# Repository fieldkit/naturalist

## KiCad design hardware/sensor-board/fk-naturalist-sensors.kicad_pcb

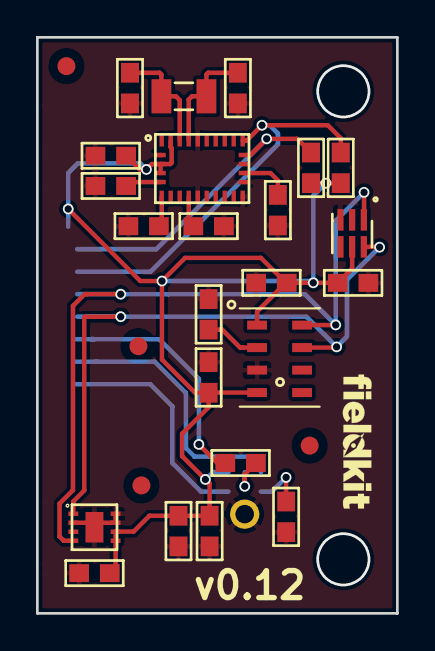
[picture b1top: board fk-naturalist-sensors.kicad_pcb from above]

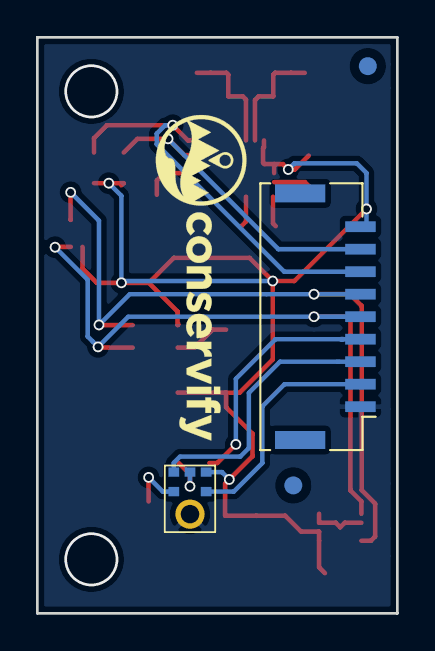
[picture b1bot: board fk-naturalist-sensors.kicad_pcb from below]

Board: 2 copper layers, 20.0 x 32.0 mm, 31 parts (4 on the bottom side), 18 nets.

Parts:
C1, C2, C3, C9, C10: 100nF; CAP-0603
C4, C6: 1uF; CAP-0603
C5: 10uF; CAP-0603
C7: 220pF; CAP-0603
C8, C11: 22pF; CAP-0603
J1: CONN_01x09; Molex_CLIK-Mate_502382-0970_1x09_P1.25mm_Vertical
M1, M2, M5, M6, M9, M10: FIDUCIAL; FIDUCIAL-1MM
R1, R3, R4, R5: 10K; RES-0603
R2: 68R; RES-0603
R6, R7: 4.7K; RES-0603
U1: MPL3115A2; DFN-8-1EP_5x2.55mm_Pitch1.25mm_98ASA002260D
U2: SHT31; SHT3x
U3: SPH0645; SPH0645LM4H-B
U4: TSL2591
U5: BNO055
Y1: FC-135; ABS07

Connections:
3V3: C2.1, C3.1, C4.1, C5.1, C6.1, C7.1, C9.2, J1.9, R6.2, R7.2, U1.1, U1.4, U2.5, U2.6, U3.5, U4.5, U5.3, U5.4, U5.28
/I2S_BCLK: J1.2, U3.4
/I2S_DATA: J1.4, R2.2
/I2S_WS: J1.3, U3.1
/SCL: J1.6, U1.8, U2.4, U4.1
/SCL2: J1.8, R7.1, U5.19
/SDA: J1.5, U1.7, U2.1, U4.6
/SDA2: J1.7, R6.1, U5.20
GND: C1.2, C2.2, C3.2, C4.2, C5.2, C6.2, C7.2, C8.2, C9.1, C10.1, C11.2, J1.1, R1.1, R3.2, R4.2, R5.2, U1.3, U2.2, U2.7, U2.8, U2.PAD, U3.3, U4.3, U5.2, U5.10, U5.15, U5.16, U5.18, U5.25
unnamed: C1.1, U1.2
unnamed: C8.1, U5.27, Y1.1
unnamed: C10.2, U5.9
unnamed: C11.1, U5.26, Y1.2
unnamed: R1.2, U3.2
unnamed: R2.1, U3.6
unnamed: R3.1, U5.17
unnamed: R4.1, U5.6
unnamed: R5.1, U5.5

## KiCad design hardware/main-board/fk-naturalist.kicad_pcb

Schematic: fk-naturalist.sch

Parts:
BT1: BATTERY_CELL; BAT_CR1210
C1, C6, C12, C21, C26, C27: 1uF; CAP-0603
C2, C32: 47uF; CAP-0603
C3, C4: 18pF; CAP-0603
C5, C7, C8, C9, C11, C13, C15, C16, C18, C33, C35: 100nF; CAP-0603
C10, C19, C20: 4.7uF; CAP-0603
C14: 4.7nF; CAP-0603
C17, C22, C24, C31, C34: 10uF; CAP-0603
C23, C29: 470pF; CAP-0603
C25, C30: 2.2uF; CAP-0603
C28: 10nF; CAP-0603
D1: Orange; LED-0603
D2, D9: Green; LED-0603
D3: Yellow; LED-0603
D7: PMEG3020CPA; SOT-1016
D8: PRTR5V0U2X; SOT-143B
D10, D11: Red; LED-0603
F1: MF-PSMF050X-2; MF-PSMF020X
J1, J11: RF-SMA-EDGE
J2, J12, J14: CONN_01x02; SJ_OPEN
J3, J10: S2B-PH-SM4-TB
J4: Conn_01x01; Socket_Strip_Straight_1x01_Pitch2.54mm
J5: CONN_01x03_SERIAL; Molex_CLIK-Mate_502382-0370_1x03_P1.25mm_Vertical
J6: CONN_01x09; Molex_CLIK-Mate_502382-0970_1x09_P1.25mm_Vertical
J7: CONN_02x05_SWD; HDR_02x05_Pitch1.27mm_SMD_SWD
J8: CONN_01x02; Molex_CLIK-Mate_502382-0270_1x02_P1.25mm_Vertical
J9: MICRO-USB
J13: CONN_01x06; JST_SH_BM06B-SRSS-TB_1x06-1MP_P1.00mm_Vertical
L1, L2, L3: BLM18KG221SN1D; IND-0603
M1, M3, M4, M6: MOUNT_HOLE; HOLE_NPTH_2.54MM
M2, M5, M8, M9, M10, M11: FIDUCIAL; FIDUCIAL-1MM
M7: MICRO-SD
Q1: 2N7002LT1G; SOT-23
R1, R2, R11, R13, R23: 100K; RES-0603
R3, R25, R33: 2K2; RES-0603
R4, R5, R37, R39, R40: 1K; RES-0603
R6, R7, R8, R17, R32, R34: 10K; RES-0603
R9, R10, R30: 330R; RES-0603
R12, R14: 165.7K; RES-0603
R21: 1K18; RES-0603
R22: 46K4; RES-0603
R24: 2K94; RES-0603
R31: 1M; RES-0603
R35, R36, R42, R43: 4.7K; RES-0603
R41: 180R; RES-0603
SW1, SW2: SPNO; SW_SPST_WURTH_1
U1: ATWINC1500-MR210PA; ATMEL_ATWINC1500-MR210PA
U2: ATSAMD21G18A-AU; TQFP-48_7x7mm_Pitch0.5mm
U3: RFM95W; RFM9xW
U4: 24AA02E64; SOT-23-5_HandSoldering
U5: S25FL116K0XMFI041; SOIC-8-N-WIDE
U6: BQ24074RGTT; QFN-16_3x3mm
U7: PCF8523; SOIC-8-N
U8, U9: TL5209; SOIC-8-N
U10: FGPMMOPA6H
U11: MAX1704XX; DFN-8-1EP_3x2mm_Pitch0.5mm
U12: TPS2052B; SOIC-8-N
U13: SK6812
U14: MCP1700T-3302E/MB; SOT-89
Y1, Y2: FC-135; ABS07

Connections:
3V3: C2.1, C5.1, C8.1, C9.1, C11.1, C13.1, C15.1, C24.1, C25.1, D1.2, J2.1, J7.1, J12.1, J14.2, L1.2, R6.2, R7.2, R8.1, R11.1, R17.1, R23.2, R35.1, R36.1, R37.1, R41.1, R42.2, U2.17, U2.36, U2.44, U3.13, U4.4 (VCC), U8.3, U12.2, U13.3, U14.3 (VOUT)
5V0: C10.1, D7.1, L2.1
/A1_WIFI_RST: R1.1, U1.4, U2.7
/A2_WIFI_IRQ: U1.13, U2.8
/A3: U2.9, U13.2
/A4_GPS_EN: U2.10, U12.3
/A5_MODULE_EN: U2.47
/BAT_BACKUP: BT1.1, J13.5, U7.3 (VBAT), U10.4 (VBACKUP)
/CHG: R33.1, U6.9 (~CHG~)
/D0_RADIO_D2: J7.4, U2.45, U3.16
/D1_RADIO_D1: J7.2, U2.46, U3.15
/D2_RADIO_D0: U2.23, U3.14
/D2_WIFI_EN: R2.1, U1.22, U2.22
/D5_RADIO_CS: U2.24, U3.5
/D6_USER_SW: R10.1, U2.29
/D7_WIFI_CS: U1.16, U2.30
/D8_WIFI_WAKE: U1.11, U2.11
/D9_MODULE_EN: U9.1
/D12_SD_CS: M7.2, U2.28
/D13: Q1.1, U2.26
/D26_FLASH_CS: U2.39, U5.1 (~CS~)
/D30: J5.3, U2.37
/D31: J5.2, U2.38
/GPS_3V3: C16.1, C17.1, J12.2, L3.1, U12.7
/GPS_FIX: D11.2, U10.5 (3D-FIX)
/GPS_RX: J13.4, U2.27, U10.10 (RX)
/GPS_TX: J13.3, U2.25, U10.9 (TX)
/I2S_BCLK: J6.2, U2.15
/I2S_DATA: J6.4, U2.12
/I2S_WS: J6.3, U2.16
/MISO: M7.7, U1.17, U2.21, U3.2, U5.2 (SO/IO1)
/MODULE_3V3: C30.1, J6.9, J14.1, R13.1, U9.3
/MOSI: M7.3, U1.15, U2.19, U3.3, U5.5 (SI/IO0)
/PERIPH_3V3: C18.1, C33.1, C34.1, D2.2, D3.2, J2.2, M7.4, U1.10, U1.20, U1.23, U5.3 (~WP~/IO2), U5.7 (~HOLD~/IO3), U5.8 (VCC), U12.6
/PERIPH_EN: U2.48, U12.4
/PG: R32.1, U6.7 (~PGOOD~)
/RESET: R9.1, U2.40
/RST: J7.10, R8.2, R9.2, SW1.2
/SCK: M7.5, U1.18, U2.20, U3.4, U5.6 (SCLK)
/SCL: J6.6, R36.2, U2.32, U4.1 (SCL), U7.6 (SCL), U11.7 (SCL)
/SCL2: J6.8, U2.14
/SDA: J6.5, R35.2, U2.31, U4.3 (SDA), U7.5 (SDA), U11.8 (SDA)
/SDA2: J6.7, U2.13
/USB+: D8.2, J9.3, U2.34
/USB-: D8.3, J9.2, U2.33
/USB_ID: R30.2, U2.41
GND: BT1.2, C1.2, C2.2, C3.1, C4.1, C5.2, C6.2, C7.2, C8.2, C9.2, C10.2, C11.2, C12.1, C13.2, C14.2, C15.2, C16.2, C17.2, C18.2, C19.2, C20.2, C21.2, C22.2, C23.2, C24.2, C25.2, C26.2, C27.2, C28.1, C29.2, C30.2, C31.1, C32.2, C33.2, C34.2, C35.2, D8.1, J1.2, J1.3, J1.4, J1.5, J3.2, J5.1, J6.1, J7.3, J7.5, J7.9, J8.1, J9.5, J10.2, J11.2, J11.3, J11.4, J11.5, J13.1, M7.6, M7.MT1, M7.MT2, Q1.2, R1.2, R2.2, R12.2, R14.2, R21.1, R22.1, R24.1, R25.1, R31.2, R34.2, R39.1, R43.2, SW1.1, SW2.1, U1.9, U1.12, U1.28, U2.5, U2.18, U2.35, U2.42, U3.1, U3.8, U3.10, U4.2 (VSS), U5.4 (VSS), U6.4 (~CE~), U6.6 (EN1), U6.8 (VSS), U6.17 (PAD), U7.4 (VSS), U8.5, U8.6, U8.7, U8.8, U9.5, U9.6, U9.7, U9.8, U10.3 (GND), U10.8 (GND), U10.12 (GND), U10.19 (GND), U11.1 (CTG), U11.4 (GND), U11.9 (GND), U12.1, U13.1, U14.1 (GND)
unnamed: C1.1, U2.4
unnamed: C3.2, U2.2, Y1.1
unnamed: C4.2, U2.1, Y1.2
unnamed: C6.1, U2.43
unnamed: C7.1, L1.1, U2.6
unnamed: C14.1, J9.7, R31.1
unnamed: C22.1, R37.2, U7.8 (VDD)
unnamed: C23.1, R11.2, R12.1, U8.4
unnamed: C27.1, R40.2, U11.2 (CELL)
unnamed: C28.2, R41.2, U11.3 (VDD)
unnamed: C29.1, R13.2, R14.1, U9.4
unnamed: C31.2, C32.1, C35.1, J13.2, L3.2, U10.1 (VCC)
unnamed: D1.1, R3.1
unnamed: D2.1, R4.2
unnamed: D3.1, R5.2
unnamed: D9.1, R32.2
unnamed: D10.1, R33.2
unnamed: D11.1, R39.2
unnamed: F1.1, L2.2
unnamed: J1.1, J4.1, U3.9
unnamed: J8.2, R10.2, R17.2, SW2.2
unnamed: J9.4, R23.1, R30.1
unnamed: J11.1, U10.11 (EX_ANT)
unnamed: Q1.3, R3.2
unnamed: R4.1, U1.26
unnamed: R5.1, U1.27
unnamed: R6.1, U12.8
unnamed: R7.1, U12.5
unnamed: R21.2, U6.12 (ILIM)
unnamed: R22.2, U6.14 (TMR)
unnamed: R24.2, U6.15 (ITERM)
unnamed: R25.2, U6.16 (ISET)
unnamed: R34.1, U6.1 (TS)
unnamed: R42.1, U11.5 (ALT)
unnamed: R43.1, U11.6 (QST)
unnamed: U7.1 (XI), Y2.2
unnamed: U7.2 (XO), Y2.1
VBAT: C19.1, J10.1, R40.1, U6.2 (BAT), U6.3 (BAT)
VBUS: C20.1, C21.1, C26.1, D9.2, D10.2, U6.5 (EN2), U6.10 (OUT), U6.11 (OUT), U8.1, U8.2, U9.2, U14.2 (VIN)
VEXT: C12.2, D7.3, U6.13 (IN)
VIN: D7.2, J3.1
VUSB: D8.4, F1.2, J9.1

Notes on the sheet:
MOUNTING
SWD/JTAG
BREAKOUT
LED
SERIAL FLASH
POWER MANAGEMENT
USB-DEVICE
MCU
TX0
RX0
VIN:5-10.5V (OVP up to 28V)
1. All capacitors are NP0/COG 50V unless specified. 2. All resistors are 62.5mW 1% unless specified.
16Mbit = 2Mbytes
M2.5 size
1.27 mm (0.05")
EN2 EN1
LOW LOW
LOW HI
HI LOW
HI HI
I-INPUT LIMIT
100mA
500mA
Set by R6:1.3A
Standby
32.768kHz
12.5pF
TX1
RX1
LEDS
24AA02E64 DEVICE ID
WIFI
GPS
POWER MANAGEMENT (3V3 REGULATOR)
I2C PULLUP
LIPO GAUGE
NOTES
RTC
RFM95W
FIDUCIALS

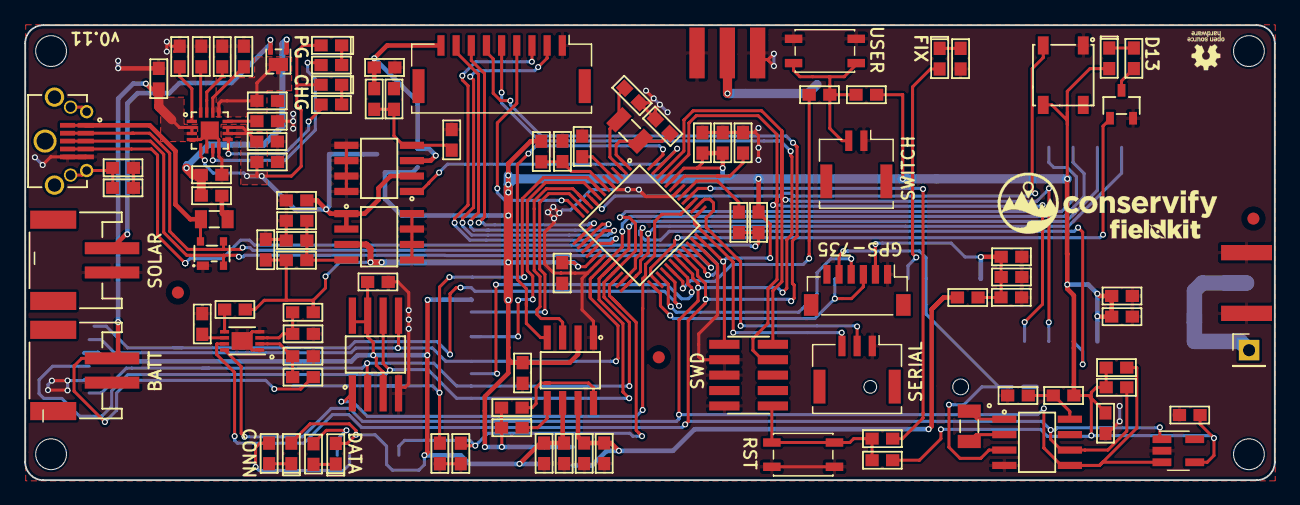
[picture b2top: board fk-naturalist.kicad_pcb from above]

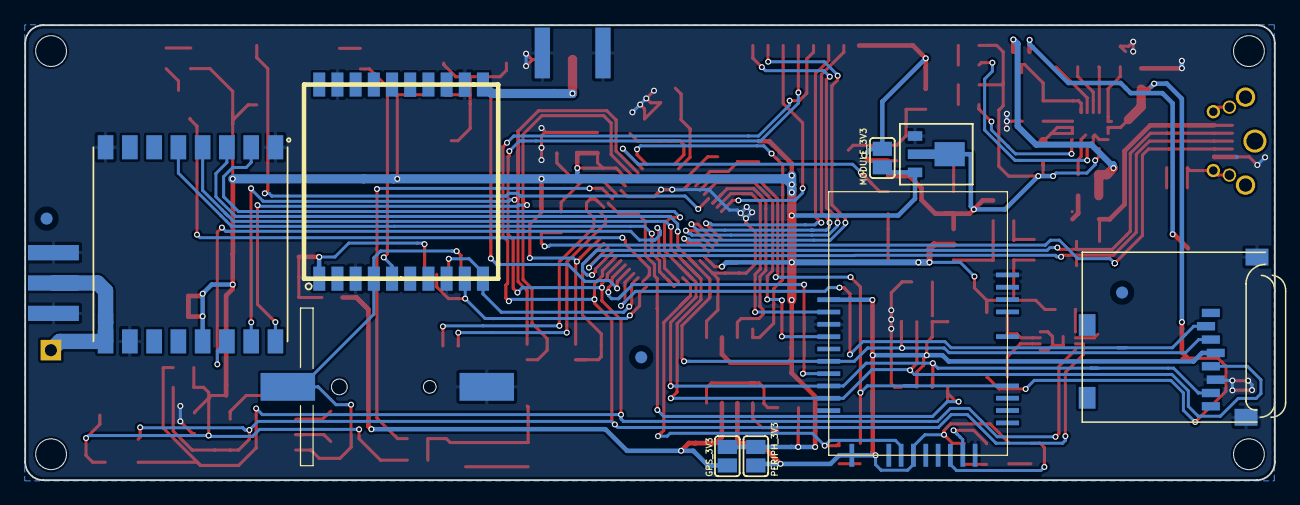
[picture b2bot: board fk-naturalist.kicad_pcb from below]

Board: 2 copper layers, 103.0 x 37.5 mm, 121 parts (13 on the bottom side), 87 nets.

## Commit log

2017-12-28 Renaming.
2017-12-28 Expose Wire1 and Wire3 on header. Got rid of unnecessary jumpers.
2017-12-28 Plotting.
2017-12-28 Just tweaking the locations of things.
2017-12-29 Adding D30 and D31 to header.
2017-12-30 Watchdog moved into Module.
2017-12-31 Adding TinyGPS library.
2017-12-31 Change to PendingReading struct.
2017-12-31 Record elapsed time.
2018-01-11 Pass which TwoWire to use for core comms.
2018-01-12 Set time on readings.
2018-01-12 Starting on the combined coreless board. Schematic is... done hopefully.
    This includes the change to the new I2S chip.
2018-01-13 Working on the new PCB layout.
2018-01-14 Everything is connected, time to cleanup.
2018-01-15 Some power fills, cleaning up warnings.
2018-01-16 Breakaway part for sensors.
2018-01-16 Remove some bad shapes.
2018-01-16 New breakaway approach. Cleaning some things up.
2018-01-18 Add data-protocol dependency.
2018-01-25 Making the schematic more organized for a presentation.
2018-02-05 Format specifier fix.
2018-02-13 Use adafruit ASFcore
2018-02-15 Use TwoWireBus wrapper to simplify bus configuration
2018-02-15 Add RTC related part numbers.
2018-02-15 Fix TSL2591 footprint.
2018-02-15 Add legacy voltage regulator, just in case. And a missing resistor.
2018-02-15 Plotting gerbers.
2018-02-16 Use forked WiFi101 library.
2018-02-16 SerialFlash version/dependency.
2018-03-02 Change module name to FkNat.
2018-03-05 Using key names for sensors. Going to pretty up using metadata.
2018-03-06 Labeling.
2018-03-06 Add test firmware for the new integrated board.
2018-03-06 More label/naming cleanup.
2018-03-06 Drop AnalogSampling stuff, going to use a different approach.
2018-03-06 Starting firmware for the consolidated board.
2018-03-06 Add linker script with noinit section.
2018-03-06 Actually gather readings in NatCore firmware.
2018-03-06 Add a config.h template
2018-03-06 Change order of test based on build order :)
2018-03-06 Log time from RTC at startup.
2018-03-06 Don't read BNO055 if it's missing.
2018-03-06 Compile firmware as core.
2018-03-07 Use SerialPort abstract for GPS.
2018-03-09 Call doneScanning after loading module state to log metadata.
2018-03-15 Default config.h template only defines if missing.
2018-03-21 Fix USB footprint with oval drills.
2018-03-21 Moving some parts in from the edge.
2018-03-21 Nudge some passives away from a sensor.
2018-03-21 Adding some pin 1 markers.
2018-03-21 Bump revision.
2018-03-22 Fix serial flash pin. It's on the "TX_LED" pin. Seems to work there.
2018-03-22 Pass flash to CoreState and initialize if necessary.
2018-03-22 Issue various warnings about PIN_LED_TXL.
2018-03-27 Fixes after changes to firmware-common.
2018-03-27 LiveData takes just a Task now.
2018-03-27 New logging interface.
2018-04-03 Set module type.
2018-04-04 Invert supervisor/parallel task container.
2018-04-06 Pass ModuleCommunications into AppServicer.
2018-04-09 Separate task queue for wifi connections.
2018-04-19 Adding CI build tag alongside Git hash.
2018-04-19 Move firmware defines into cmake.
2018-04-19 Disable verbose makefile.
2018-04-19 Long git hash.
2018-04-19 Use taskQueue for sensor readings.
2018-04-27 Add lwstreams dependency.
2018-04-27 Project name, disable verbose makefile.
2018-04-30 Adding RadioHead library.
2018-04-30 Add lora comms dependency.
2018-05-01 Switch to our RadioHead fork.
2018-05-01 Migrate to arduino-logging.
2018-05-04 Enable the radio on FkNat.
2018-05-05 Fix getting gitdeps in the build.
2018-05-07 Adding peripheral enable NFET.
2018-05-08 Use fkfs to test SD to avoid formatting issues causing false negatives.
2018-05-08 Fix stencil on audio chip and plotting.
2018-05-08 Add check for the SPH0645 chip.
2018-05-11 Split main.cpp up into separate files.
2018-05-11 Dropping module code. No longer relevant.
2018-05-14 Calculate some audio information and include that in readings.
    Still trying to find a good metric/value here. Not totally happy with the
    quality of this data, yet.
2018-05-14 Add transmit file task back.
2018-05-14 Include min/max RMS as well.
2018-05-15 Wider transmit interval.
2018-05-17 New tuning variable name.
2018-05-18 Do flash test after other top components.
2018-05-18 Enable peripherals using our new switch.
2018-05-19 Adding some part numbers.
2018-05-20 Use generated seed.h include.
2018-05-21 Only overwrite blank network configurations at startup.
2018-05-22 Fix some float narrowing warnings.
2018-05-22 Run restartWizard after we're logging to SD.
2018-05-22 Enable call trace debugging stuff.
    This required me to add some dependencies to the test firmware.
2018-06-13 Widen gap between USB and SD. Nudge USB out.
    Giovanni recommended we make these changes to ease our enclosure design.
2018-06-13 Preparing to split the PCB into two boards.
2018-06-13 Add separate sensors PCB.
2018-06-13 Remove sensors from main board. Add connector.
2018-06-15 Adding fiducials.
2018-06-15 Adding fiducials to the sensor board.
2018-06-15 Using new SPH0645 footprint.
2018-06-18 A new image.
2018-06-19 Replot gerbers.
2018-06-19 Fix traces on MCU and via in pads on some ICs.
    Replot with aux origin on drills.
2018-06-20 Plot sensor board.
2018-06-25 Add Leds to status ctor.
2018-06-27 Adding fiducials to the bottom.
2018-06-27 Fix soldermask clearance on sensor board and plot.
2018-06-27 Add phylum dependency.
2018-06-27 Fix solder mask clearances correctly.
2018-06-27 Adding dimensions.
2018-06-29 Fix ctor after phylum changes.
2018-06-29 Convert memzero to memset.
2018-07-01 Update to use new phylum based flash storage state manager.
2018-07-08 Startup stuff specific to the FSM changes.
2018-07-08 Use fk_uptime instead of millis.
2018-07-10 Wifi ctor.
2018-07-13 Pass Watchdog to FlashStorage.
2018-07-14 Using SimpleLog, some other Core stuff.
2018-07-14 Standardizing startup.
2018-07-20 Add live data manager.
2018-07-24 Upgrade to Kicad 5. Add SK6812.
2018-07-24 Add lwcron dependency.
2018-07-25 Update to use new lwcron scheduler code.
2018-07-29 Update startup to use same code as Core.
2018-07-30 Use latest dependencies.
2018-07-30 Include state header directly.
2018-07-31 Add number of readings and module name to info.
2018-07-31 Use getModule to get module to set readings for.
2018-07-31 Use new allocation strategy for ModuleInfo.
2018-08-02 Ignore dependencies.cmake
2018-08-03 Add Jenkinsfile.
2018-08-08 Moving archive files.
2018-08-08 Fix build dependencies.
2018-08-09 Use shared build properties.
2018-08-11 Compile flags to enable flash in phylum.
2018-08-13 Compile flags for phylum.
2018-08-15 Fixup linker scripts to resemble core.
2018-08-15 Archive and distribute binaries.
2018-08-15 Use task.h instead of active_object.h
2018-08-21 Switch to new Arduino CMake module.
2018-08-22 Use helpers in FkCore to define dependencies. This is still eh.
2018-08-22 Set FK_NATURALIST, write profile.
2018-08-22 Consistent part values across our schematics.
2018-08-22 Part updates.
2018-08-23 Move to footprints in our library.
2018-08-23 Fix SK6812.
2018-08-24 Use repository URLs for deps.
2018-08-24 Use tools name for dependencies.sd.
2018-08-24 Main board is now same as fk-core.
2018-08-24 Fix DRC checks and rescued parts.
2018-08-24 Add BNO055 to sensor board. Larger connector.
2018-08-24 Add new 9 pin sensor connector.
2018-08-25 Drop debug here, collides with common now.
2018-08-28 Plot gerbers.
2018-08-28 Use more compatible FP for flash.
2018-08-28 Consistency in part values
2018-08-28 Add NeoPixel dependency, upgrade WiFi.
2018-08-29 Fit sensor board schematic into frame.
2018-08-29 Set ModuleInfo for FkNat sensors.
2018-08-29 Cleanup schematic wks.
2018-08-29 Rename to avoid collision with function.
2018-08-30 Fix SD landing.
2018-08-31 Link to ArduinoSound.
2018-08-31 Add .gdbinit file.
2018-08-31 Config is dumped in common now.
2018-08-31 State for gathering readings.
2018-08-31 Only setup readings once.
2018-08-31 Naming style.
2018-08-31 Initialize sensors during startup.
2018-08-31 Fix name of binary to be like other profiled ones.
2018-08-31 Formatting.
2018-08-31 Enable wifi only at startup by default.
2018-09-03 Fix archive and distribution paths.
2018-09-07 Add some bypass caps on GPS 3v3, see if fix issues are power related.
2018-09-07 Add a bead on the GPS 3v3 supply too.
2018-09-07 Plot and bump version.
2018-09-17 Use newer configurable states approach.
2018-09-20 Fix Rx/Tx on backup GPS.
2018-09-25 Include path hack to get build working on OSX.
    Case insensitive file systems are annoying.
2018-09-26 Pin to newer library versions.
2018-10-04 Fix linking issues.
2018-10-09 Label positions for assembly, use better footprints for sensors.
2018-10-09 Enable modules/peripherals and GPS. Use logging library.
2018-10-09 Make core and fknat tests more similar.
2018-10-09 Naturalist module enable pin is A5, D9 is used for I2S.
2018-12-12 Fix make jobserver warnings.
2019-01-14 Main board is now the same as Core, deleting to avoid confusion.
2019-01-14 Inherit from CheckCore to check Naturalist.
2019-01-15 Updating test harness code. Report sample readings.
2019-01-15 Adding pullups to SDA2/SCL2.
2019-01-16 Namespace tweaks in main.
2019-01-16 Conditional compile on the BNO055
2019-01-17 Fix location of a fudicial.
2019-02-08 Unnecessary namespace.
2019-02-08 Copying common core test code.
2019-02-08 Add config.h template to the test build for wifi time syncing.
2019-02-22 Use similar approach to network configuration as Core.
2019-02-25 Use ArduinoSound that works with newer SAMD cores.
2019-03-14 Standardized hole diameters, pushed connector away from board edge, and panelized for production.
2019-03-28 Copy check_core from core repository.
2019-03-28 Try to initialize sensors a few times. Sometimes doesn't take?
2019-03-28 Scripts for programming.
2019-03-28 Update the LEDs when taking FkNat readings.
2019-04-23 Use absolute BUILD in Makefile.
2019-05-07 We use versions of these from the cmake repo.
2019-05-08 Keep USB serial around.
2019-05-14 Initialize I2S with the other sensors.
2019-05-16 Better reporting on sensor checks in test firmware.
2019-05-16 Some tweaks to the flash helper scripts.
2019-05-22 Get rid of sleeps in flash scripts.
2019-05-22 Leave peripherals on.
2019-05-24 Fix path to bootloader.
2019-06-21 Paths in flasher tool.
2019-07-19 Fix log output.
2019-07-29 Segger RTT dependency.
2019-07-29 Disable restart wizard.
    This was hanging and since this is before the WDT it's bad. Also, this isn't
    totally useful.
2019-07-30 Add log prefix to RTT logs.
2019-10-12 Fix dependency in test.
